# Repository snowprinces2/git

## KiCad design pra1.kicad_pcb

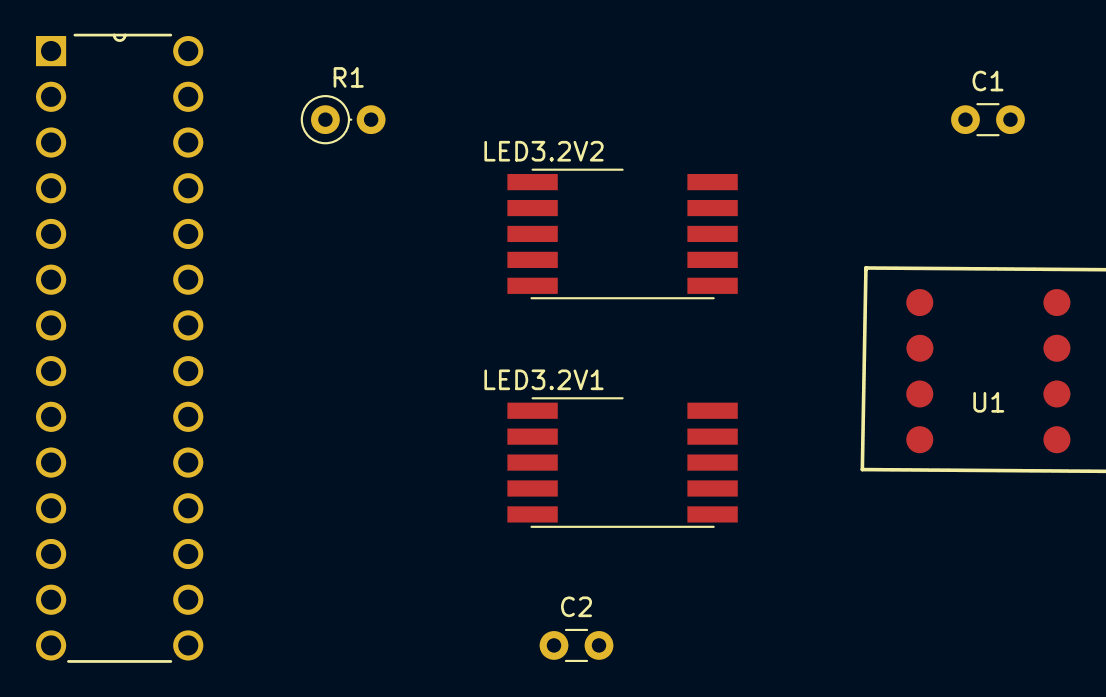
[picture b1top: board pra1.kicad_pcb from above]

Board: 2 copper layers, 7 parts (0 on the bottom side), 18 nets, no tracks yet.

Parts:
C1, C2: 0.1u; C_Disc_D3.0mm_W1.6mm_P2.50mm
IC1: ATMEGA168-20PU?Arduino; DIP254P762X457-28
LED3.2V1, LED3.2V2: 10-PA5; KCSC02-136
R1: 10k; R_Axial_DIN0207_L6.3mm_D2.5mm_P2.54mm_Vertical
U1: AE-SCP1000-D01; SCP1000-D01

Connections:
GND: C1.2, C2.2, IC1.8, IC1.22, U1.1, U1.2, U1.4
unnamed: C2.1, IC1.21
unnamed: IC1.1, R1.1
unnamed: IC1.4, LED3.2V1.7, LED3.2V2.7
unnamed: IC1.5, LED3.2V1.6, LED3.2V2.6
unnamed: IC1.6, LED3.2V1.4, LED3.2V2.4
unnamed: IC1.11, LED3.2V1.2, LED3.2V2.2
unnamed: IC1.12, LED3.2V1.1, LED3.2V2.1
unnamed: IC1.13, LED3.2V1.9, LED3.2V2.9
unnamed: IC1.14, LED3.2V1.10, LED3.2V2.10
unnamed: IC1.15, LED3.2V1.5, LED3.2V2.5
unnamed: IC1.16, U1.7
unnamed: IC1.17, U1.5
unnamed: IC1.18, U1.6
unnamed: IC1.19, U1.3
unnamed: IC1.23, LED3.2V2.3, LED3.2V2.8
unnamed: IC1.24, LED3.2V1.3, LED3.2V1.8
VCC: C1.1, IC1.7, IC1.20, R1.2, U1.8

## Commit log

2018-03-28 新規ファイル
